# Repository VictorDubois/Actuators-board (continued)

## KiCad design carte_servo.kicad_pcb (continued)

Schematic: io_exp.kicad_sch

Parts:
C34: 2.2uF; C_0805_2012Metric; LCSC# C19110
J4, J26, J27, J28: Conn_01x03; JST_XH_B3B-XH-A_1x03_P2.50mm_Vertical; LCSC# C144394
R40, R43, R45, R47: 3.3V; R_0603_1608Metric
R41, R42, R44, R46: 12V; R_0603_1608Metric
R50: 10kR; R_0603_1608Metric; LCSC# C2930027
R55, R58, R60, R62: 22kR; R_0603_1608Metric; LCSC# C2907128
R56, R57, R59, R61: 56.2kR; R_0603_1608Metric; LCSC# C2930117
U11: PCF8574ATS; SSOP-20_4.4x6.5mm_P0.65mm; LCSC# C2803277

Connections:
3.3V: C34.1, R40.1, R43.1, R45.1, R47.1, R50.1, U11.5 (VDD); also elsewhere on the board
/IO_expander/SIG_0: R55.1, R56.2, U11.10 (P0)
/IO_expander/SIG_1: R57.1, R58.1, U11.11 (P1)
/IO_expander/SIG_2: R59.2, R60.1, U11.12 (P2)
/IO_expander/SIG_3: R61.2, R62.1, U11.14 (P3)
BATT_12V_elec: R41.1, R42.1, R44.1, R46.1; also elsewhere on the board
GND: C34.2, J4.1, J26.1, J27.1, J28.1, R55.2, R58.2, R60.2, R62.2, U11.6 (A0), U11.7 (A1), U11.9 (A2), U11.15 (VSS); also elsewhere on the board
I2C_extra_2: U11.20 (P7); also elsewhere on the board
unnamed: J4.2, R40.2, R41.2
unnamed: J4.3, R56.1
unnamed: J26.2, R42.2, R43.2
unnamed: J26.3, R57.2
unnamed: J27.2, R44.2, R45.2
unnamed: J27.3, R59.1
unnamed: J28.2, R46.2, R47.2
unnamed: J28.3, R61.1
unnamed: R50.2, U11.1 (~INT)
SCL: U11.2 (SCL); also elsewhere on the board
SDA: U11.4 (SDA); also elsewhere on the board
TRANSISTOR_1: U11.16 (P4); also elsewhere on the board
TRANSISTOR_3: U11.17 (P5); also elsewhere on the board
TRANSISTOR_4: U11.19 (P6); also elsewhere on the board

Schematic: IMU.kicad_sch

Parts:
C36: 2.2nF; C_0603_1608Metric; LCSC# C14663
C37, C38, C39: 100nF; C_0603_1608Metric; LCSC# C14663
U12: MPU-6050; InvenSense_QFN-24_4x4mm_P0.5mm

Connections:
3.3V: C37.1, C39.1, U12.8 (VLOGIC), U12.13 (VDD); also elsewhere on the board
GND: C36.2, C37.2, C38.1, C39.2, U12.1 (CLKIN), U12.9 (AD0), U12.11 (FSYNC), U12.18 (GND); also elsewhere on the board
unnamed: C36.1, U12.20 (CPOUT)
unnamed: C38.2, U12.10 (REGOUT)
SCL: U12.23 (SCL); also elsewhere on the board
SDA: U12.24 (SDA); also elsewhere on the board

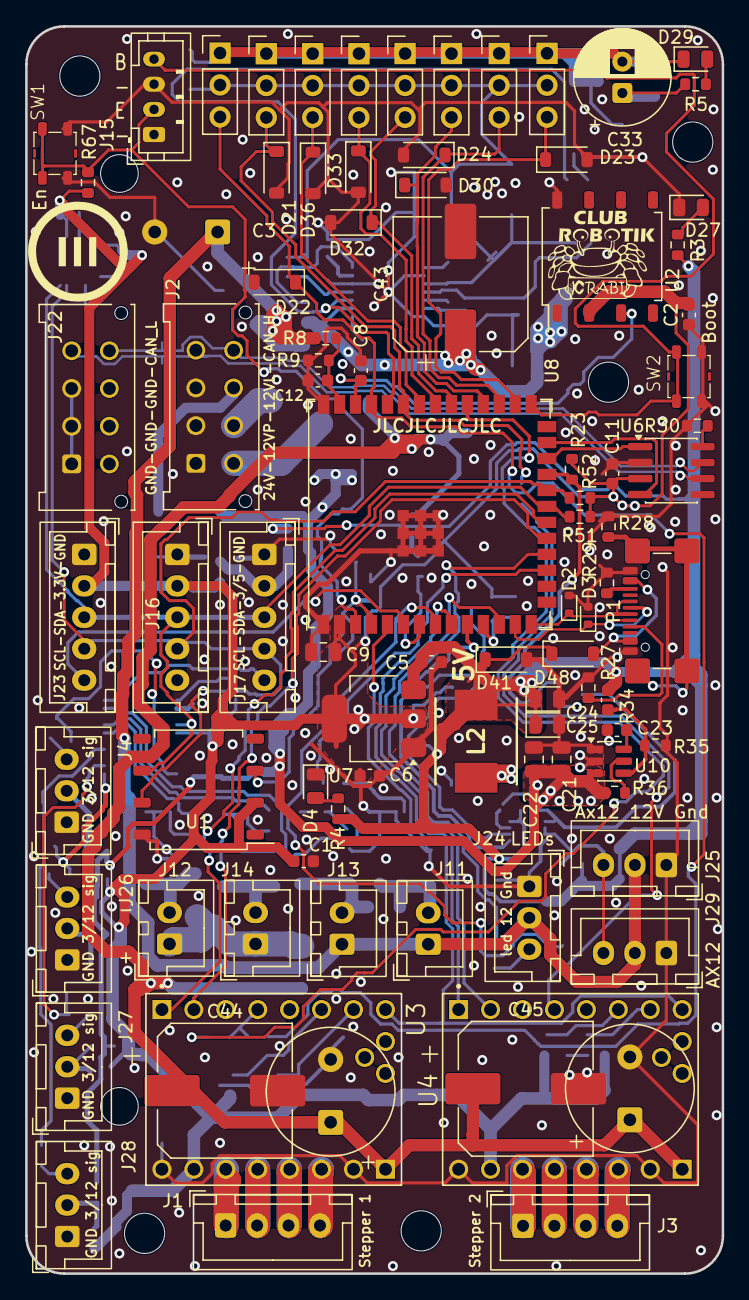
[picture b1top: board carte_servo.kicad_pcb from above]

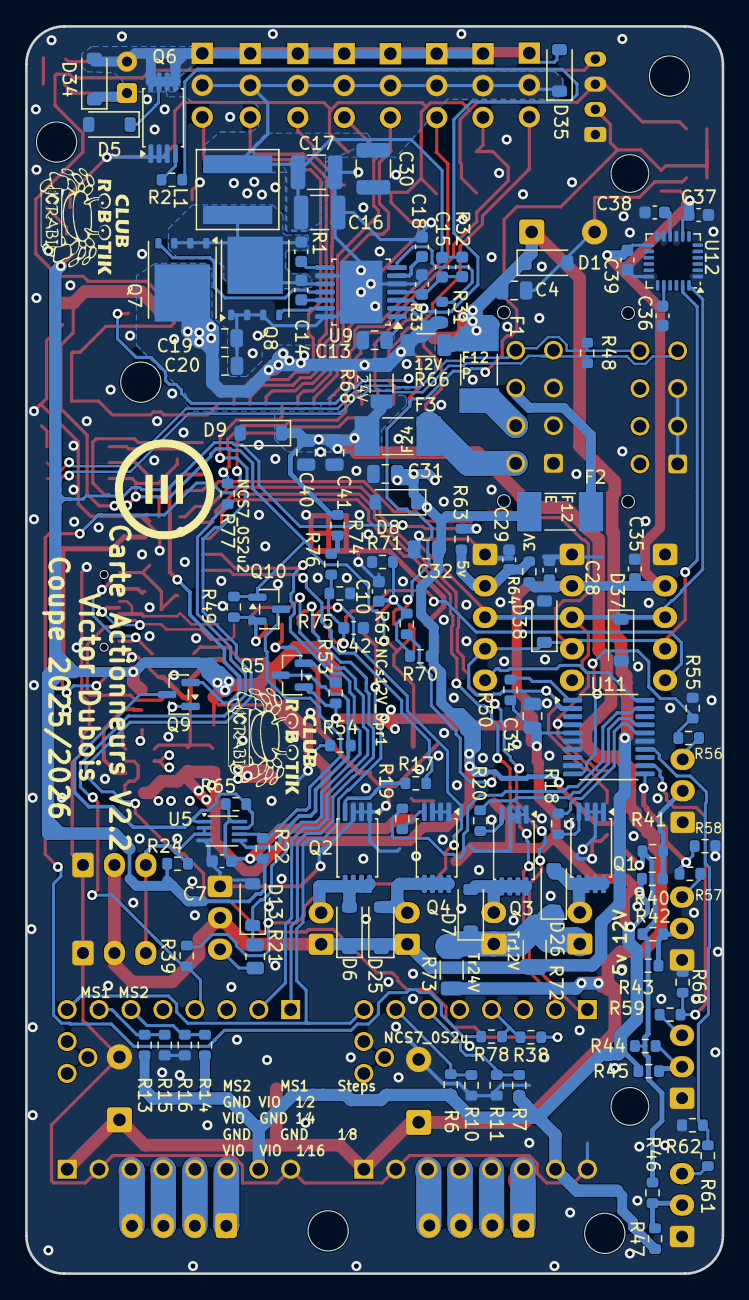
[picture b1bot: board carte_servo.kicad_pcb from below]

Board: 4 copper layers, 55.4 x 99.2 mm, 213 parts (114 on the bottom side), 120 nets.

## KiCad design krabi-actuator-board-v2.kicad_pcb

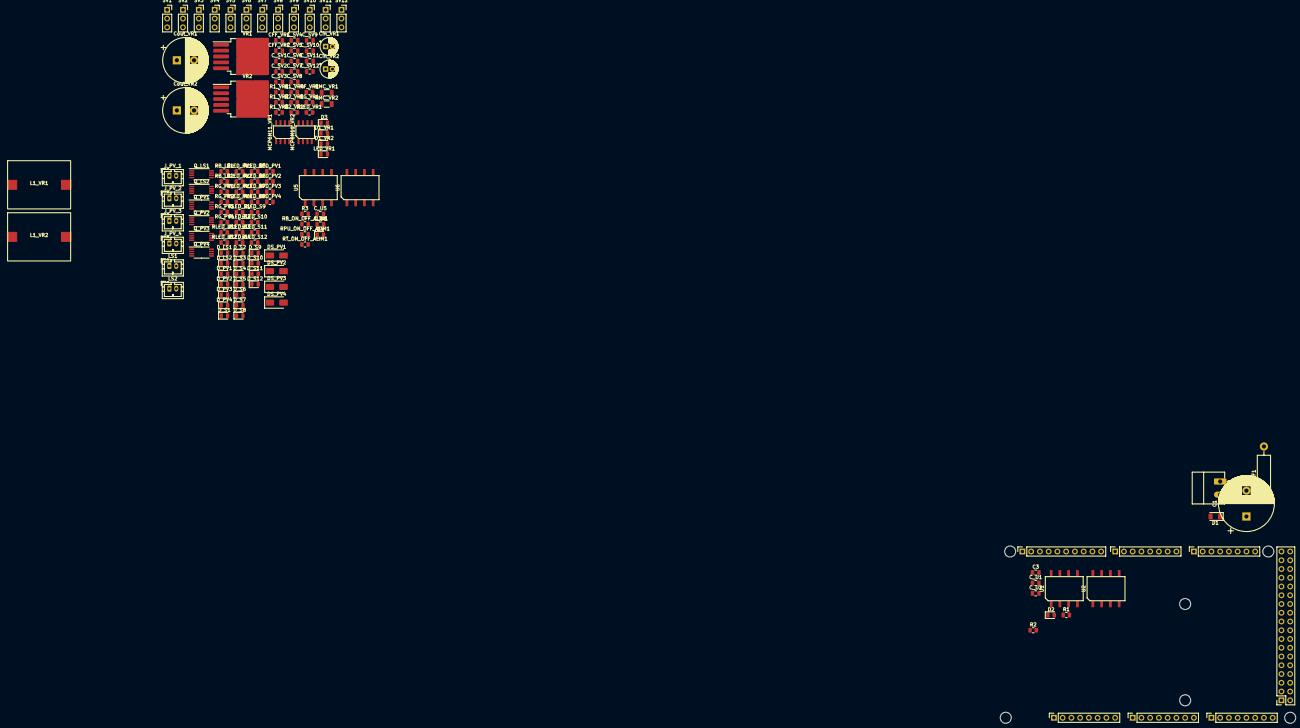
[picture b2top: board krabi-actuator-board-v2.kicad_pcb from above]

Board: 2 copper layers, 147 parts (0 on the bottom side), 78 nets, no tracks yet.

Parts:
C1: 1mF; CP_Radial_D16.0mm_P7.50mm
C3: 100nF; C_0805_2012Metric
CFF_VR1, CFF_VR2: 3.3nF; C_0805_2012Metric
C_SV1, C_SV2, C_SV3, C_SV4, C_SV5, C_SV6, C_SV7, C_SV8, C_SV9, C_SV10, C_SV11, C_SV12: 100nF; C_0805_2012Metric
C_U1, C_U2, C_U5, C_U6: 10pF; C_0805_2012Metric
Cin_VR1, Cin_VR2: 470µF; CP_Radial_D5.0mm_P2.00mm
Cout_VR1, Cout_VR2: 470µF; CP_Radial_D13.0mm_P5.00mm
D1: 13V; D_1206_3216Metric
D1_VR1, D1_VR2: 20V 5A; D_0805_2012Metric
D2, D3, D4: LED; LED_0805_2012Metric
DS_PV1, DS_PV2, DS_PV3, DS_PV4: D_Schottky 20V 1A; D_SMA
D_LS1, D_LS2: LED; LED_0805_2012Metric
D_PV1, D_PV2, D_PV3, D_PV4: LED; LED_0805_2012Metric
D_S1, D_S2, D_S3, D_S4, D_S5, D_S6, D_S7, D_S8, D_S9, D_S10, D_S11, D_S12: LED; LED_0805_2012Metric
F1: Fuse; R_Axial_DIN0411_L9.9mm_D3.6mm_P15.24mm_Horizontal
J1: Power; PinSocket_1x08_P2.54mm_Vertical
J2: PWM; PinSocket_1x10_P2.54mm_Vertical
J3, J5: Analog; PinSocket_1x08_P2.54mm_Vertical
J4: PWM; PinSocket_1x08_P2.54mm_Vertical
J6: Communication; PinSocket_1x08_P2.54mm_Vertical
J7: Digital; PinSocket_2x18_P2.54mm_Vertical
J8: Conn_01x02_Pin; PhoenixContact_MC_1,5_2-G-3.81_1x02_P3.81mm_Horizontal
J_PV_1, J_PV_2, J_PV_3, J_PV_4: JST_PH_B2B-PH-K_1x02_P2.00mm_Vertical
L1_VR1, L1_VR2: 33µH; BOURSPM5022
LED_VR1: LED; LED_0805_2012Metric
LS1, LS2: Conn_01x02_Pin; JST_PH_B2B-PH-K_1x02_P2.00mm_Vertical
MCP6N11_VR1, MCP6N11_VR2: G10; SOIC-8-1.27x5.4m
MH1, MH2, MH3, MH4, MH5, MH6: MountingHole_3.2mm
Q_LS1, Q_LS2: DMN2011UTS; TSSOP-8_4.4x3mm_P0.65mm
Q_PV1, Q_PV2, Q_PV3, Q_PV4: DMN2011UTS; TSSOP-8_4.4x3mm_P0.65mm
R1: 253; R_0805_2012Metric
R1_VR1, R1_VR2: 38.8k; R_0805_2012Metric
R1_VR3: 50k; R_0805_2012Metric
R1_VR4: 100; R_0805_2012Metric
R2: 320; R_0805_2012Metric
R2_VR1, R2_VR2: 10k; R_0805_2012Metric
R3: 720; R_0805_2012Metric
RB_LS1, RB_LS2: 1.2k; R_0805_2012Metric
RB_ON_OFF_ALIM1: 6.65k; R_0805_2012Metric
RF_VR1: 50k; R_0805_2012Metric
RG_PV1, RG_PV2, RG_PV3, RG_PV4: 50; R_0805_2012Metric
RG_VR1: 100; R_0805_2012Metric
RLED_LS1, RLED_LS2: 720; R_0805_2012Metric
RLED_PV1, RLED_PV2, RLED_PV3, RLED_PV4: 720; R_0805_2012Metric
RLED_S1, RLED_S2, RLED_S3, RLED_S4, RLED_S5, RLED_S6, RLED_S7, RLED_S8, RLED_S9, RLED_S10, RLED_S11, RLED_S12: 320; R_0805_2012Metric
RLED_VR1: 320; R_0805_2012Metric
RMC_VR1, RMC_VR2: 10m (250mW); R_1206_3216Metric
RPD_PV1, RPD_PV2, RPD_PV3, RPD_PV4: 10k; R_0805_2012Metric
RPU_ON_OFF_ALIM1: 20k; R_0805_2012Metric
RT_ON_OFF_ALIM1: 20k; R_0805_2012Metric
SV1, SV2, SV3, SV4, SV5, SV6, SV7, SV8, SV9, SV10, SV11, SV12: Conn_01x03_Pin; PinSocket_1x03_P2.54mm_Vertical
U1, U2, U5, U6: XGZP6897D_differential_pressure_sensor; SOIC-8-11mmx7mm outside pad 1.9
VR1, VR2: LM2596s; TO-263-5_TabPin6

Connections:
6V1: LED_VR1.1 (K), MCP6N11_VR1.2 (VIM), MCP6N11_VR1.7 (VDD), MCP6N11_VR1.8 (EN/nCAL), RMC_VR1.2
6V2: D3.1 (K), MCP6N11_VR2.2 (VIM), MCP6N11_VR2.7 (VDD), MCP6N11_VR2.8 (EN/nCAL), RMC_VR2.2
6V_1: C_SV1.1, C_SV2.1, C_SV3.1, C_SV4.1, C_SV5.1, C_SV6.1, SV1.2, SV2.2, SV3.2, SV4.2, SV5.2, SV6.2
6V_2: C_SV7.1, C_SV8.1, C_SV9.1, C_SV10.1, C_SV11.1, C_SV12.1, SV7.2, SV8.2, SV9.2, SV10.2, SV11.2, SV12.2
12V: C1.1, Cin_VR1.1, Cin_VR2.1, D1.1 (K), D4.1 (K), D_PV1.1 (K), D_PV2.1 (K), D_PV3.1 (K), D_PV4.1 (K), F1.2, J_PV_1.1, J_PV_2.1, J_PV_3.1, J_PV_4.1, LS1.2, LS2.2, RT_ON_OFF_ALIM1.1, VR1.1 (Vin), VR2.1 (Vin)
+5V: C3.1, C_U1.1, C_U2.1, C_U5.1, C_U6.1, D2.1 (K), J1.5, J7.35, J7.36, U1.2 (Vdd), U2.2 (Vdd), U5.2 (Vdd), U6.2 (Vdd)
CON_PV1: J7.33, RG_PV1.1
CON_PV2: J7.34, RG_PV2.1
CON_PV3: J7.31, RG_PV3.1
CON_PV4: J7.32, RG_PV4.1
CURRENT_VR1: J3.2, MCP6N11_VR1.6 (VOUT), RF_VR1.1
CURRENT_VR2: J3.1, MCP6N11_VR2.6 (VOUT), R1_VR3.1
GND: C1.2, C3.2, C_SV1.2, C_SV2.2, C_SV3.2, C_SV4.2, C_SV5.2, C_SV6.2, C_SV7.2, C_SV8.2, C_SV9.2, C_SV10.2, C_SV11.2, C_SV12.2, C_U1.2, C_U2.2, C_U5.2, C_U6.2, Cin_VR1.2, Cin_VR2.2, Cout_VR1.2, Cout_VR2.2, D1.2 (A), D1_VR1.2 (A), D1_VR2.2 (A), J1.6, J1.7, J2.4, J7.1, J7.2, J8.2, MCP6N11_VR1.4 (VSS), MCP6N11_VR1.5 (VREF), MCP6N11_VR2.4 (VSS), MCP6N11_VR2.5 (VREF), Q_LS1.1 (S), Q_LS2.1 (S), R1.2, R1_VR4.2, R2.2, R2_VR1.2, R2_VR2.2, R3.2, RB_ON_OFF_ALIM1.2, RG_VR1.2, RLED_LS1.2, RLED_LS2.2, RLED_S1.2, RLED_S2.2, RLED_S3.2, RLED_S4.2, RLED_S5.2, RLED_S6.2, RLED_S7.2, RLED_S8.2, RLED_S9.2, RLED_S10.2, RLED_S11.2, RLED_S12.2, RLED_VR1.2, SV1.3, SV2.3, SV3.3, SV4.3, SV5.3, SV6.3, SV7.3, SV8.3, SV9.3, SV10.3, SV11.3, SV12.3, U1.8 (GND), U2.8 (GND), U5.8 (GND), U6.8 (GND), VR1.3 (GND), VR2.3 (GND)
LEDS_1: J7.22, RB_LS1.1
LEDS_2: J7.20, RB_LS2.1
unnamed: CFF_VR1.1, D1_VR1.1 (K), L1_VR1.1, R1_VR1.1, VR1.2 (Ouput)
unnamed: CFF_VR2.1, D1_VR2.1 (K), L1_VR2.1, R1_VR2.1, VR2.2 (Ouput)
unnamed: D2.2 (A), R1.1
unnamed: D3.2 (A), R2.1
unnamed: D4.2 (A), R3.1
unnamed: DS_PV1.2 (A), Q_PV1.1 (S), Q_PV1.2 (S), Q_PV1.3 (S), RPD_PV1.1
unnamed: DS_PV1.1 (K), J_PV_1.2, Q_PV1.5 (D), Q_PV1.6 (D), Q_PV1.7 (D), Q_PV1.8 (D), RLED_PV1.2
unnamed: DS_PV2.2 (A), Q_PV2.1 (S), Q_PV2.2 (S), Q_PV2.3 (S), RPD_PV2.1
unnamed: DS_PV2.1 (K), J_PV_2.2, Q_PV2.5 (D), Q_PV2.6 (D), Q_PV2.7 (D), Q_PV2.8 (D), RLED_PV2.2
unnamed: DS_PV3.2 (A), Q_PV3.1 (S), Q_PV3.2 (S), Q_PV3.3 (S), RPD_PV3.1
unnamed: DS_PV3.1 (K), J_PV_3.2, Q_PV3.5 (D), Q_PV3.6 (D), Q_PV3.7 (D), Q_PV3.8 (D), RLED_PV3.2
unnamed: DS_PV4.2 (A), Q_PV4.1 (S), Q_PV4.2 (S), Q_PV4.3 (S), RPD_PV4.1
unnamed: DS_PV4.1 (K), J_PV_4.2, Q_PV4.5 (D), Q_PV4.6 (D), Q_PV4.7 (D), Q_PV4.8 (D), RLED_PV4.2
unnamed: D_LS1.2 (A), RLED_LS1.1
unnamed: D_LS1.1 (K), LS1.1, Q_LS1.5 (D)
unnamed: D_LS2.2 (A), RLED_LS2.1
unnamed: D_LS2.1 (K), LS2.1, Q_LS2.5 (D)
unnamed: D_PV1.2 (A), RLED_PV1.1
unnamed: D_PV2.2 (A), RLED_PV2.1
unnamed: D_PV3.2 (A), RLED_PV3.1
unnamed: D_PV4.2 (A), RLED_PV4.1
unnamed: D_S1.2 (A), RLED_S1.1
unnamed: D_S2.2 (A), RLED_S2.1
unnamed: D_S3.2 (A), RLED_S3.1
unnamed: D_S4.2 (A), RLED_S4.1
unnamed: D_S5.2 (A), RLED_S5.1
unnamed: D_S6.2 (A), RLED_S6.1
unnamed: D_S7.2 (A), RLED_S7.1
unnamed: D_S8.2 (A), RLED_S8.1
unnamed: D_S9.2 (A), RLED_S9.1
unnamed: D_S10.2 (A), RLED_S10.1
unnamed: D_S11.2 (A), RLED_S11.1
unnamed: D_S12.2 (A), RLED_S12.1
unnamed: F1.1, J8.1
unnamed: LED_VR1.2 (A), RLED_VR1.1
unnamed: MCP6N11_VR1.1 (VFG), RF_VR1.2, RG_VR1.1
unnamed: Cout_VR1.1, L1_VR1.2, MCP6N11_VR1.3 (VIP), RMC_VR1.1
unnamed: MCP6N11_VR2.1 (VFG), R1_VR3.2, R1_VR4.1
unnamed: Cout_VR2.1, L1_VR2.2, MCP6N11_VR2.3 (VIP), RMC_VR2.1
unnamed: Q_LS1.4 (G), RB_LS1.2
unnamed: Q_LS2.4 (G), RB_LS2.2
unnamed: Q_PV1.4 (G), RG_PV1.2, RPD_PV1.2
unnamed: Q_PV2.4 (G), RG_PV2.2, RPD_PV2.2
unnamed: Q_PV3.4 (G), RG_PV3.2, RPD_PV3.2
unnamed: Q_PV4.4 (G), RG_PV4.2, RPD_PV4.2
unnamed: RB_ON_OFF_ALIM1.1, RPU_ON_OFF_ALIM1.1, RT_ON_OFF_ALIM1.2
unnamed: CFF_VR1.2, R1_VR1.2, R2_VR1.1, VR1.4 (Feedback)
unnamed: CFF_VR2.2, R1_VR2.2, R2_VR2.1, VR2.4 (Feedback)
ON/OFF: J4.2, RPU_ON_OFF_ALIM1.2, VR1.5 (ON/OFF), VR2.5 (ON/OFF)
SCL: J2.1, J6.8, U1.7 (SCL), U2.7 (SCL), U5.7 (SCL), U6.7 (SCL)
SDA: J2.2, J6.7, U1.6 (SDA), U2.6 (SDA), U5.6 (SDA), U6.6 (SDA)
SERVO_1: D_S1.1 (K), J4.8, SV1.1
SERVO_2: D_S2.1 (K), J4.7, SV2.1
SERVO_3: D_S3.1 (K), J4.6, SV3.1
SERVO_4: D_S4.1 (K), J4.5, SV4.1
SERVO_5: D_S5.1 (K), J4.4, SV5.1
SERVO_6: D_S6.1 (K), J4.3, SV6.1
SERVO_7: D_S7.1 (K), J4.1, SV7.1
SERVO_8: D_S8.1 (K), J2.10, SV8.1
SERVO_9: D_S9.1 (K), J2.9, SV9.1
SERVO_10: D_S10.1 (K), J2.8, SV10.1
SERVO_11: D_S11.1 (K), J2.7, SV11.1
SERVO_12: D_S12.1 (K), J2.6, SV12.1

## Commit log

2022-03-21 creation
2022-04-10 version without mega I2C pins
2022-04-15 use mega I2C port
2022-04-16 small fixes
2022-04-17 add 2 servos + possibility to measure Vbatt
2022-04-20 JST_PH=>JST_XH. Version envoyee en fab
2022-05-12 specify values + BOM
2022-10-08 [WiP] debut de V2
2023-07-25 Start v2 board: arduino Mega shield base, and input power
2023-07-25 Add LTSpice simu
2023-07-25 Adding SOIC for the pressure sensors
2023-07-27 Full command of the servos 6V power
2023-07-27 Add Power ON leds
2023-07-27 Servos are connecteds
2023-07-28 Add Vaccum pump output and control
2023-07-28 Measure the current of the Power supplies
2023-07-28 Update servo with capa & add led strip page
2023-07-28 adding LED strip
2023-07-28 Add 2 led strip & led visualisation on all outputs
2023-09-19 Assigning footprints to schemas
2023-09-19 Fixing bad association and symbols*
2023-10-04 fix driving servo power (NMOS on GND) + fix 12V connector position
2023-10-13 add AX12 connector + LED strip connector + libraries todo : add 12V connectors, change stepper connectors
2023-10-26 add second AX12 connector + change stepper connectors + add 12V connector. Todo : add SPI for RFID
2023-10-29 Add SPI connector + route control pins (LEDs, AX12)
2023-10-30 add zeners for new connections
2023-10-30 4 layers
2023-10-30 Change to SOD-123 diodes
2023-11-02 route STEP and DIR for both stepper motors
2023-11-02 remove bad vias
2025-01-03 WiP start switching to an ESP32
2025-01-29 start adapting to new connectors
2025-01-29 remove intra-board zeners
2025-01-29 start placing components from scratch
2025-02-02 add DCDC 6V
2025-02-02 add self
2025-02-08 small stuff
2025-02-08 add DCDC 5V
2025-02-08 add ESD diodes for USB
2025-02-09 fix warnings + separate enable for Steppers
2025-02-09 change fuse + start servo order + routing
2025-02-09 continue routing
2025-02-10 continue routing. Shorter SW_6V and 12V from connector to big capa
2025-02-15 basic routing
2025-02-15 widen 12V/5V
2025-02-16 add vias and stuff
2025-02-16 (fields_autoplaced yes)
2025-02-16 add mounting holes
2025-02-16 add power status LEDs
2025-02-16 12V logic for ESP32 + add legends + fine tune
2025-02-22 fix warnings + add internal layers + add Uart to steppers (TX only
2025-02-22 export bom as CSV
2025-02-22 add capa for servos
2025-02-22 fix warnings, change USB-C and button
2025-02-22 fine tuning
2025-02-28 fine-tuning (move 5V away from SW_6V)
2025-02-28 add registration holes
2025-03-01 add edge of stencil
2025-03-02 add registration holes to paste layers
2025-03-02 update BOM
2025-03-02 -10% for stencil
2025-03-02 fix DCDC5V schematic
2025-03-02 SW_5V is internal layer
2025-03-06 better routing
2025-03-06 add io_exp (sch)
2025-03-06 [WiP] add expander
2025-03-07 finish routing IO_exp + some fine-tuning
2025-03-08 fine-tuning
2025-03-09 Add BOM
    Add LCSC reference and correct few footprint acording bom
2025-03-09 fix 1 error + warnings, mainly silkscreen
2025-03-09 improve DCDC current routing
2025-04-21 fix 3.3V/5V compatibility + add 120Ohms + add I2C pullups
2025-04-21 [WiP] start add MPU6050
2025-04-22 Go to 3.3V + fix io_exp + routing
2025-04-23 v1.1 2025 (=v2.1)
2025-05-12 add values
2025-05-12 add 3.3V/5V conversion on AX12 RX/TX enable
2025-06-27 fix previous commit
2025-06-27 Huge cleanup of the schematic
2025-08-24 prepare DCDC 24V compatibility + add reset/boot connector
2025-08-27 fix error + add fuse/resistor choice servo DCDC vin = 12V or 24V
2025-09-28 minor changes??
2025-10-27 fix AX12 RX: add proper 3.3V/5V level shifter
2025-10-27 add missing pullup on IO_exp INT
2025-10-27 add 12V elec measure
2025-10-28 add possibility to have 2 of the transistor outputs to use either 12V or 24V
2025-10-28 add 24V monitoring, move transistor4 to IO_exp (former I2C extra 1)
2025-10-29 tuning + add silkscreen
2025-11-02 3.3V steppers
2025-12-30 update to Kicad 9 + small fixes
2025-12-30 fix warnings + add big capa on 6V DCDC input
2026-02-05 update BOM + add big capas (do not take DNP into account)
2026-02-05 fix DNP (was just for checking what was to be bought)
2026-02-05 fix dnp
2026-02-06 change capacitor references to support >25V
2026-05-21 Add project overview and resources to README
    Added detailed description of the ESP32-based PCB features and links to the code repository and online viewer.
2026-06-20 update to Kicad 10 + start fixing warnings
2026-06-28 fix diodes on transistors + fix warnings
